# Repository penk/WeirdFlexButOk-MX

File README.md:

## WeirdFlexButOk - MX version

A hot-swappable, ergo monoblock split keyboard with tenting.

Similar to the [Choc version](https://github.com/penk/WeirdFlexButOk), this keyboard features a `0.8mm` PCB with serpentine routing (kerf cuts) near the thumb clusters. These cuts allow the board to flex along the contour of the 3D printed case, forming a `20°` tilt and `10°` tent from a single PCB.

## Features

- Hot-swappable ergo monoblock split in MX spacing
- Built-in tenting (10°) and tilting (20°) from a single FR-4 PCB
- Breakable pinky columns, for 36 or 42-key layouts 
- Optional RGB underglow LEDs

## Bill of Materials (BOM)

Quantity | Item
--- | ---
1 | Enamel pin badge (Optional)
1 | RP2040-Zero 
1 | WeirdFlexButOk-MX PCB
1 | WeirdFlexButOk-MX case & plate
36 (42) | MX Switches
36 (42) | MX Hot-swap sockets
36 (42) | 1N4148SOD-123 diodes
4 | WS2812B LEDs (Optional)
8 | M2x4 heat-set thread inserts
6 | M2x10 standoffs
14 | M2x6 screws

## Production Files

To place an order for the WeirdFlexButOk-MX PCB:

- Use the Gerber files available in the [production/](production/) folder.
- Optionally, the [BOM](production/BOM.csv) and [CPL](production/CPL.csv) files can be utilized with a PCBA service. All components, including the RP2040-Zero, are soldered to the bottom side of the board.

Ensure you select the following specifications so the PCB can flex:

- Base Material: `FR4`
- PCB Thickness: `0.8mm`

The complete PCB design project is available in the [kicad/](kicad/) folder.

## 3D Printable Files

Print the case using the provided [STL files](case/) for the 36-key (3x5) or 42-key (3x6) layout respectively.

I like to start with translucent filament and add a mid-print filament change at around `10mm` height to let the LEDs shine through the bottom part. In Cura, this feature can be found under `Extensions` -> `Post Processing` -> `Modify G-Code` -> `Add a Script` -> `Filament Change`.

Expect some amount of support material. Tolerances must be tuned for the switches (`14.2x14.2mm`) to fit properly.

I find the following parameters work best for my print:

- Top/Bottom Speed: 30 mm/s
- Support Structure: Tree
- Fan Speed Override: True
- Support Skin Fan Speed: 100%

## Firmware

Precompiled VIA-enabled firmware:

- Flash [penk_weirdflexbutok_mx_default.uf2](firmware/penk_weirdflexbutok_mx_default.uf2) to the RP2040-Zero.
- Load the [via.json](firmware/QMK/keyboards/weirdflexbutok_mx/via.json) file in `Design` tab for [VIA](https://usevia.app) configuration.

QMK source is available under [firmware/QMK/keyboards/weirdflexbutok_mx](firmware/QMK/keyboards/weirdflexbutok_mx).

## Copyright and License
Copyright (c) 2024 Penk Chen. All rights reserved.

All files are licensed under the MIT license. For more information, see the [LICENSE](LICENSE).

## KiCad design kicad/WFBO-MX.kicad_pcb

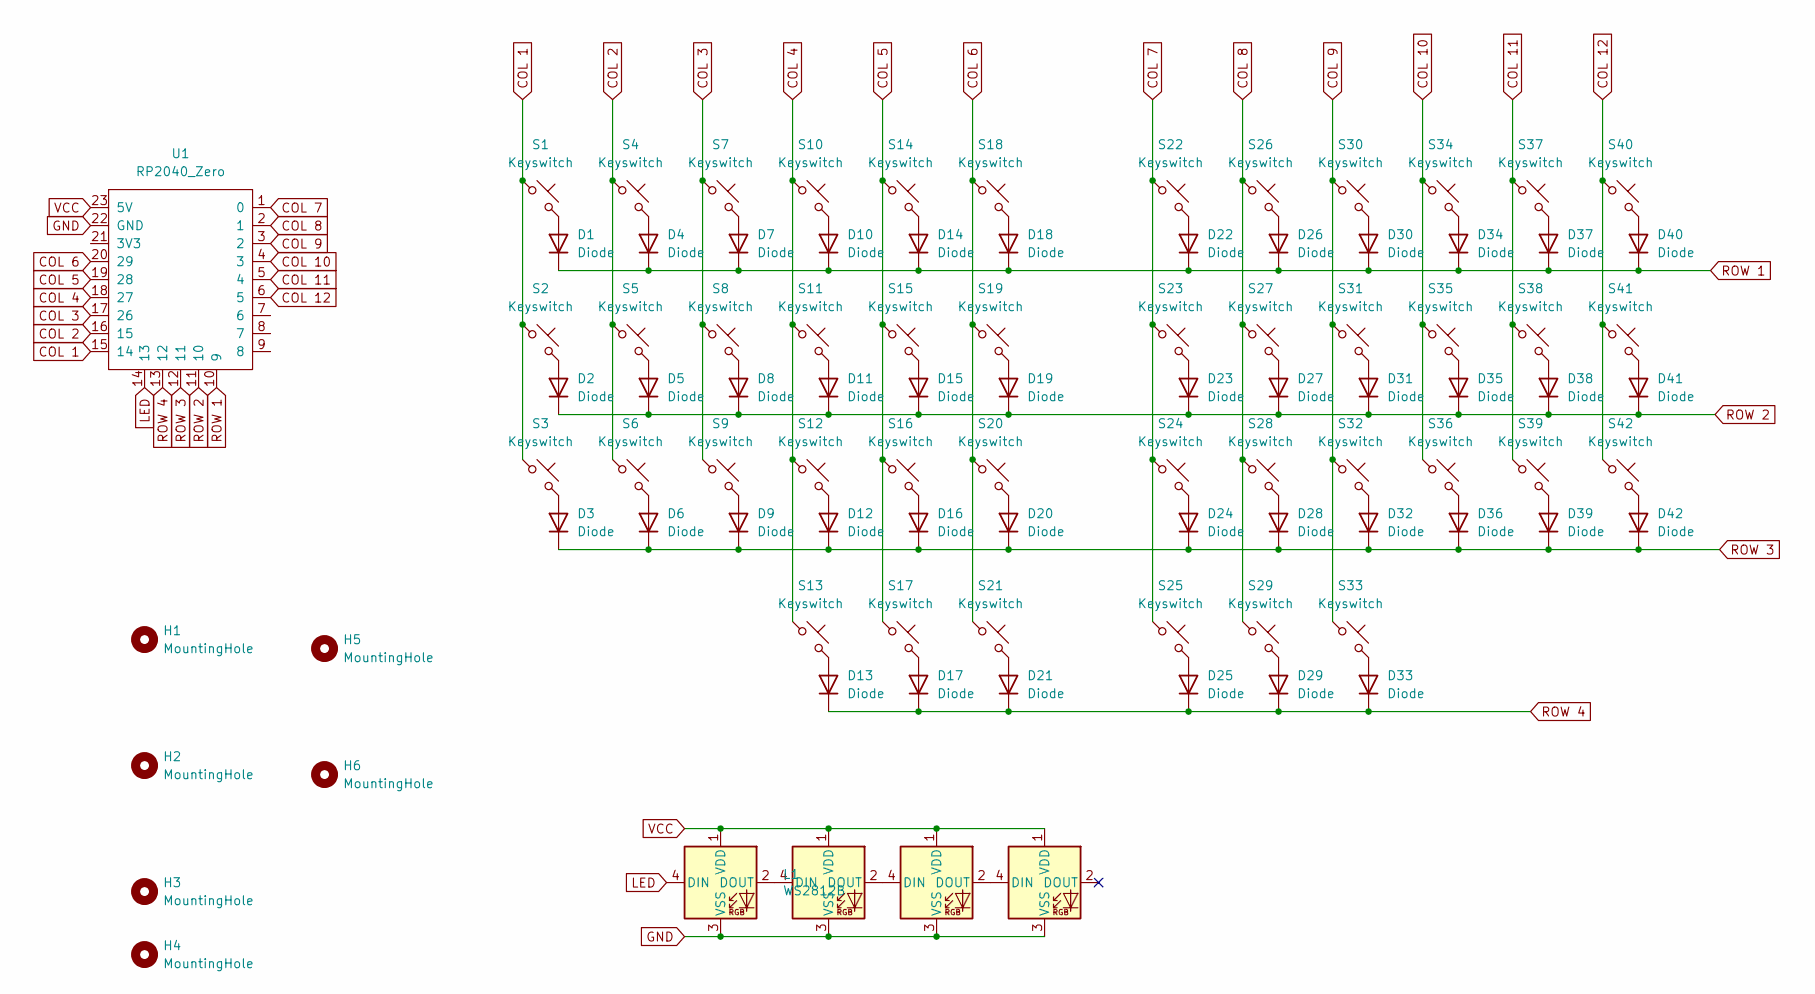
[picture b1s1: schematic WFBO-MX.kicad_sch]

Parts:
D1, D2, D3, D4, D5, D6, D7, D8, D9, D10, D11, D12, D13, D14, D15, D16, D17, D18, D19, D20, D21, D22, D23, D24, D25, D26, D27, D28, D29, D30, D31, D32, D33, D34, D35, D36, D37, D38, D39, D40, D41, D42: Diode; Diode_SOD-123
H1, H2, H3, H4, H5, H6: MountingHole; MountingHole_2.2mm_M2
L1, L2, L3, L4: WS2812B; LED_WS2812B_PLCC4_5.0x5.0mm_P3.2mm
S1, S2, S3, S4, S5, S6, S7, S8, S9, S10, S11, S12, S13, S14, S15, S16, S17, S18, S19, S20, S21, S22, S23, S24, S25, S26, S27, S28, S29, S30, S31, S32, S33, S34, S35, S36, S37, S38, S39, S40, S41, S42: Keyswitch; SW_MX_HS_1u
U1: RP2040_Zero

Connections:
COL 1: S1.1, S2.1, S3.1, U1.15 (14)
COL 2: S4.1, S5.1, S6.1, U1.16 (15)
COL 3: S7.1, S8.1, S9.1, U1.17 (26)
COL 4: S10.1, S11.1, S12.1, S13.1, U1.18 (27)
COL 5: S14.1, S15.1, S16.1, S17.1, U1.19 (28)
COL 6: S18.1, S19.1, S20.1, S21.1, U1.20 (29)
COL 7: S22.1, S23.1, S24.1, S25.1, U1.1 (0)
COL 8: S26.1, S27.1, S28.1, S29.1, U1.2 (1)
COL 9: S30.1, S31.1, S32.1, S33.1, U1.3 (2)
COL 10: S34.1, S35.1, S36.1, U1.4 (3)
COL 11: S37.1, S38.1, S39.1, U1.5 (4)
COL 12: S40.1, S41.1, S42.1, U1.6 (5)
GND: L1.3 (VSS), L2.3 (VSS), L3.3 (VSS), L4.3 (VSS), U1.22 (GND)
LED: L1.4 (DIN), U1.14 (13)
unnamed: D1.2 (A), S1.2
unnamed: D2.2 (A), S2.2
unnamed: D3.2 (A), S3.2
unnamed: D4.2 (A), S4.2
unnamed: D5.2 (A), S5.2
unnamed: D6.2 (A), S6.2
unnamed: D7.2 (A), S7.2
unnamed: D8.2 (A), S8.2
unnamed: D9.2 (A), S9.2
unnamed: D10.2 (A), S10.2
unnamed: D11.2 (A), S11.2
unnamed: D12.2 (A), S12.2
unnamed: D13.2 (A), S13.2
unnamed: D14.2 (A), S14.2
unnamed: D15.2 (A), S15.2
unnamed: D16.2 (A), S16.2
unnamed: D17.2 (A), S17.2
unnamed: D18.2 (A), S18.2
unnamed: D19.2 (A), S19.2
unnamed: D20.2 (A), S20.2
unnamed: D21.2 (A), S21.2
unnamed: D22.2 (A), S22.2
unnamed: D23.2 (A), S23.2
unnamed: D24.2 (A), S24.2
unnamed: D25.2 (A), S25.2
unnamed: D26.2 (A), S26.2
unnamed: D27.2 (A), S27.2
unnamed: D28.2 (A), S28.2
unnamed: D29.2 (A), S29.2
unnamed: D30.2 (A), S30.2
unnamed: D31.2 (A), S31.2
unnamed: D32.2 (A), S32.2
unnamed: D33.2 (A), S33.2
unnamed: D34.2 (A), S34.2
unnamed: D35.2 (A), S35.2
unnamed: D36.2 (A), S36.2
unnamed: D37.2 (A), S37.2
unnamed: D38.2 (A), S38.2
unnamed: D39.2 (A), S39.2
unnamed: D40.2 (A), S40.2
unnamed: D41.2 (A), S41.2
unnamed: D42.2 (A), S42.2
unnamed: L1.2 (DOUT), L2.4 (DIN)
unnamed: L2.2 (DOUT), L3.4 (DIN)
unnamed: L3.2 (DOUT), L4.4 (DIN)
ROW 1: D1.1 (K), D4.1 (K), D7.1 (K), D10.1 (K), D14.1 (K), D18.1 (K), D22.1 (K), D26.1 (K), D30.1 (K), D34.1 (K), D37.1 (K), D40.1 (K), U1.10 (9)
ROW 2: D2.1 (K), D5.1 (K), D8.1 (K), D11.1 (K), D15.1 (K), D19.1 (K), D23.1 (K), D27.1 (K), D31.1 (K), D35.1 (K), D38.1 (K), D41.1 (K), U1.11 (10)
ROW 3: D3.1 (K), D6.1 (K), D9.1 (K), D12.1 (K), D16.1 (K), D20.1 (K), D24.1 (K), D28.1 (K), D32.1 (K), D36.1 (K), D39.1 (K), D42.1 (K), U1.12 (11)
ROW 4: D13.1 (K), D17.1 (K), D21.1 (K), D25.1 (K), D29.1 (K), D33.1 (K), U1.13 (12)
VCC: L1.1 (VDD), L2.1 (VDD), L3.1 (VDD), L4.1 (VDD), U1.23 (5V)

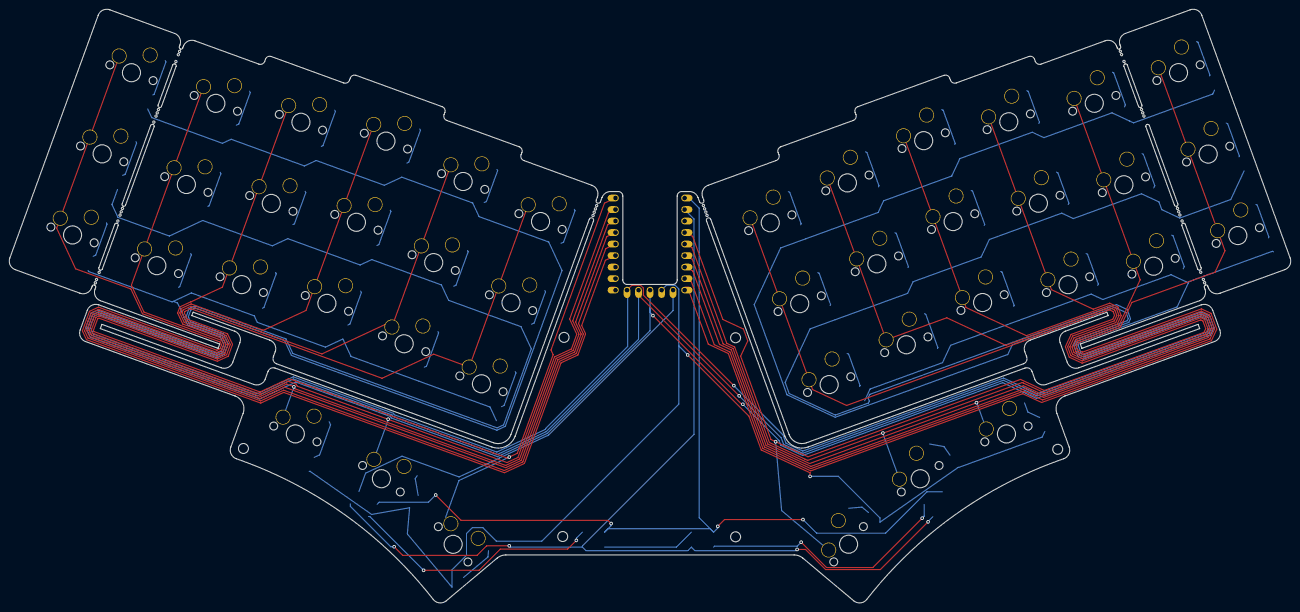
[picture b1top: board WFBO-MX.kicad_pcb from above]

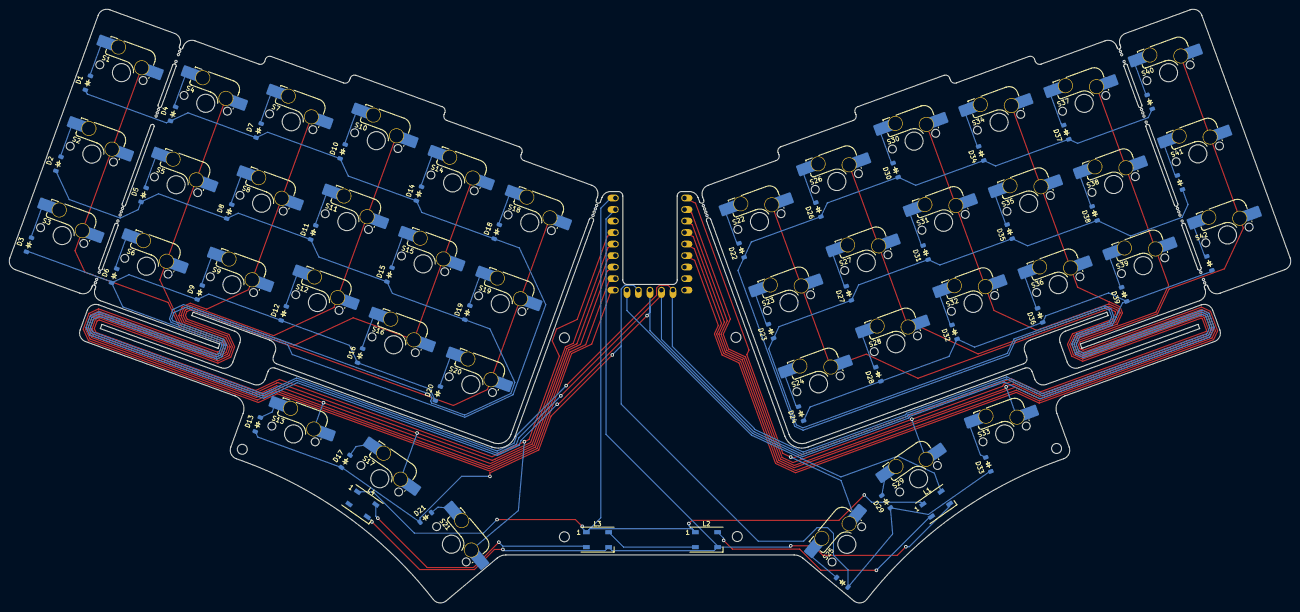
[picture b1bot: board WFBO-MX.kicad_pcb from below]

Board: 2 copper layers, 282.7 x 131.0 mm, 95 parts (89 on the bottom side), 64 nets.

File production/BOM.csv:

Designator,Footprint,Quantity,Value,LCSC Part #
"D1, D10, D11, D12, D13, D14, D15, D16, D17, D18, D19, D2, D20, D21, D22, D23, D24, D25, D26, D27, D28, D29, D3, D30, D31, D32, D33, D34, D35, D36, D37, D38, D39, D4, D40, D41, D42, D5, D6, D7, D8, D9",Diode_SOD-123,42,1N4148SOD-123,C2972760
"L1, L2, L3, L4",LED_WS2812B_PLCC4_5.0x5.0mm_P3.2mm,4,WS2812B,C2761795
"S1, S10, S11, S12, S13, S14, S15, S16, S17, S18, S19, S2, S20, S21, S22, S23, S24, S25, S26, S27, S28, S29, S3, S30, S31, S32, S33, S34, S35, S36, S37, S38, S39, S4, S40, S41, S42, S5, S6, S7, S8, S9",SW_MX_HS_1u,42,CPG151101S11-16,C5156480
